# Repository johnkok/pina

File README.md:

# PINA Project - Raspberry Pico-w energy meter

The aim of this project it to create a ultra precise energy meter based on INA228 TI's energy meter device. INA228 is a 20-bit energy meter device, with I2C host interface capable of measuring voltage/current/energy at sampling rates up to 20KHz. Device is connected with a Raspberry Pico W host acquiring the data from the I2C interface and communicating with the host through the WiFi interface using a TCP protocol. In addition, the Pico w module will be able to store IO level on DUT (Device Under Test) and transmit the data to the host application.  
  
On the host side, a basic driver implemented for libsigrok for communicating with the Pico W firmware and propagating the data to sigrok suite. Patched version of sigrok library located at the following location: https://github.com/johnkok/libsigrok

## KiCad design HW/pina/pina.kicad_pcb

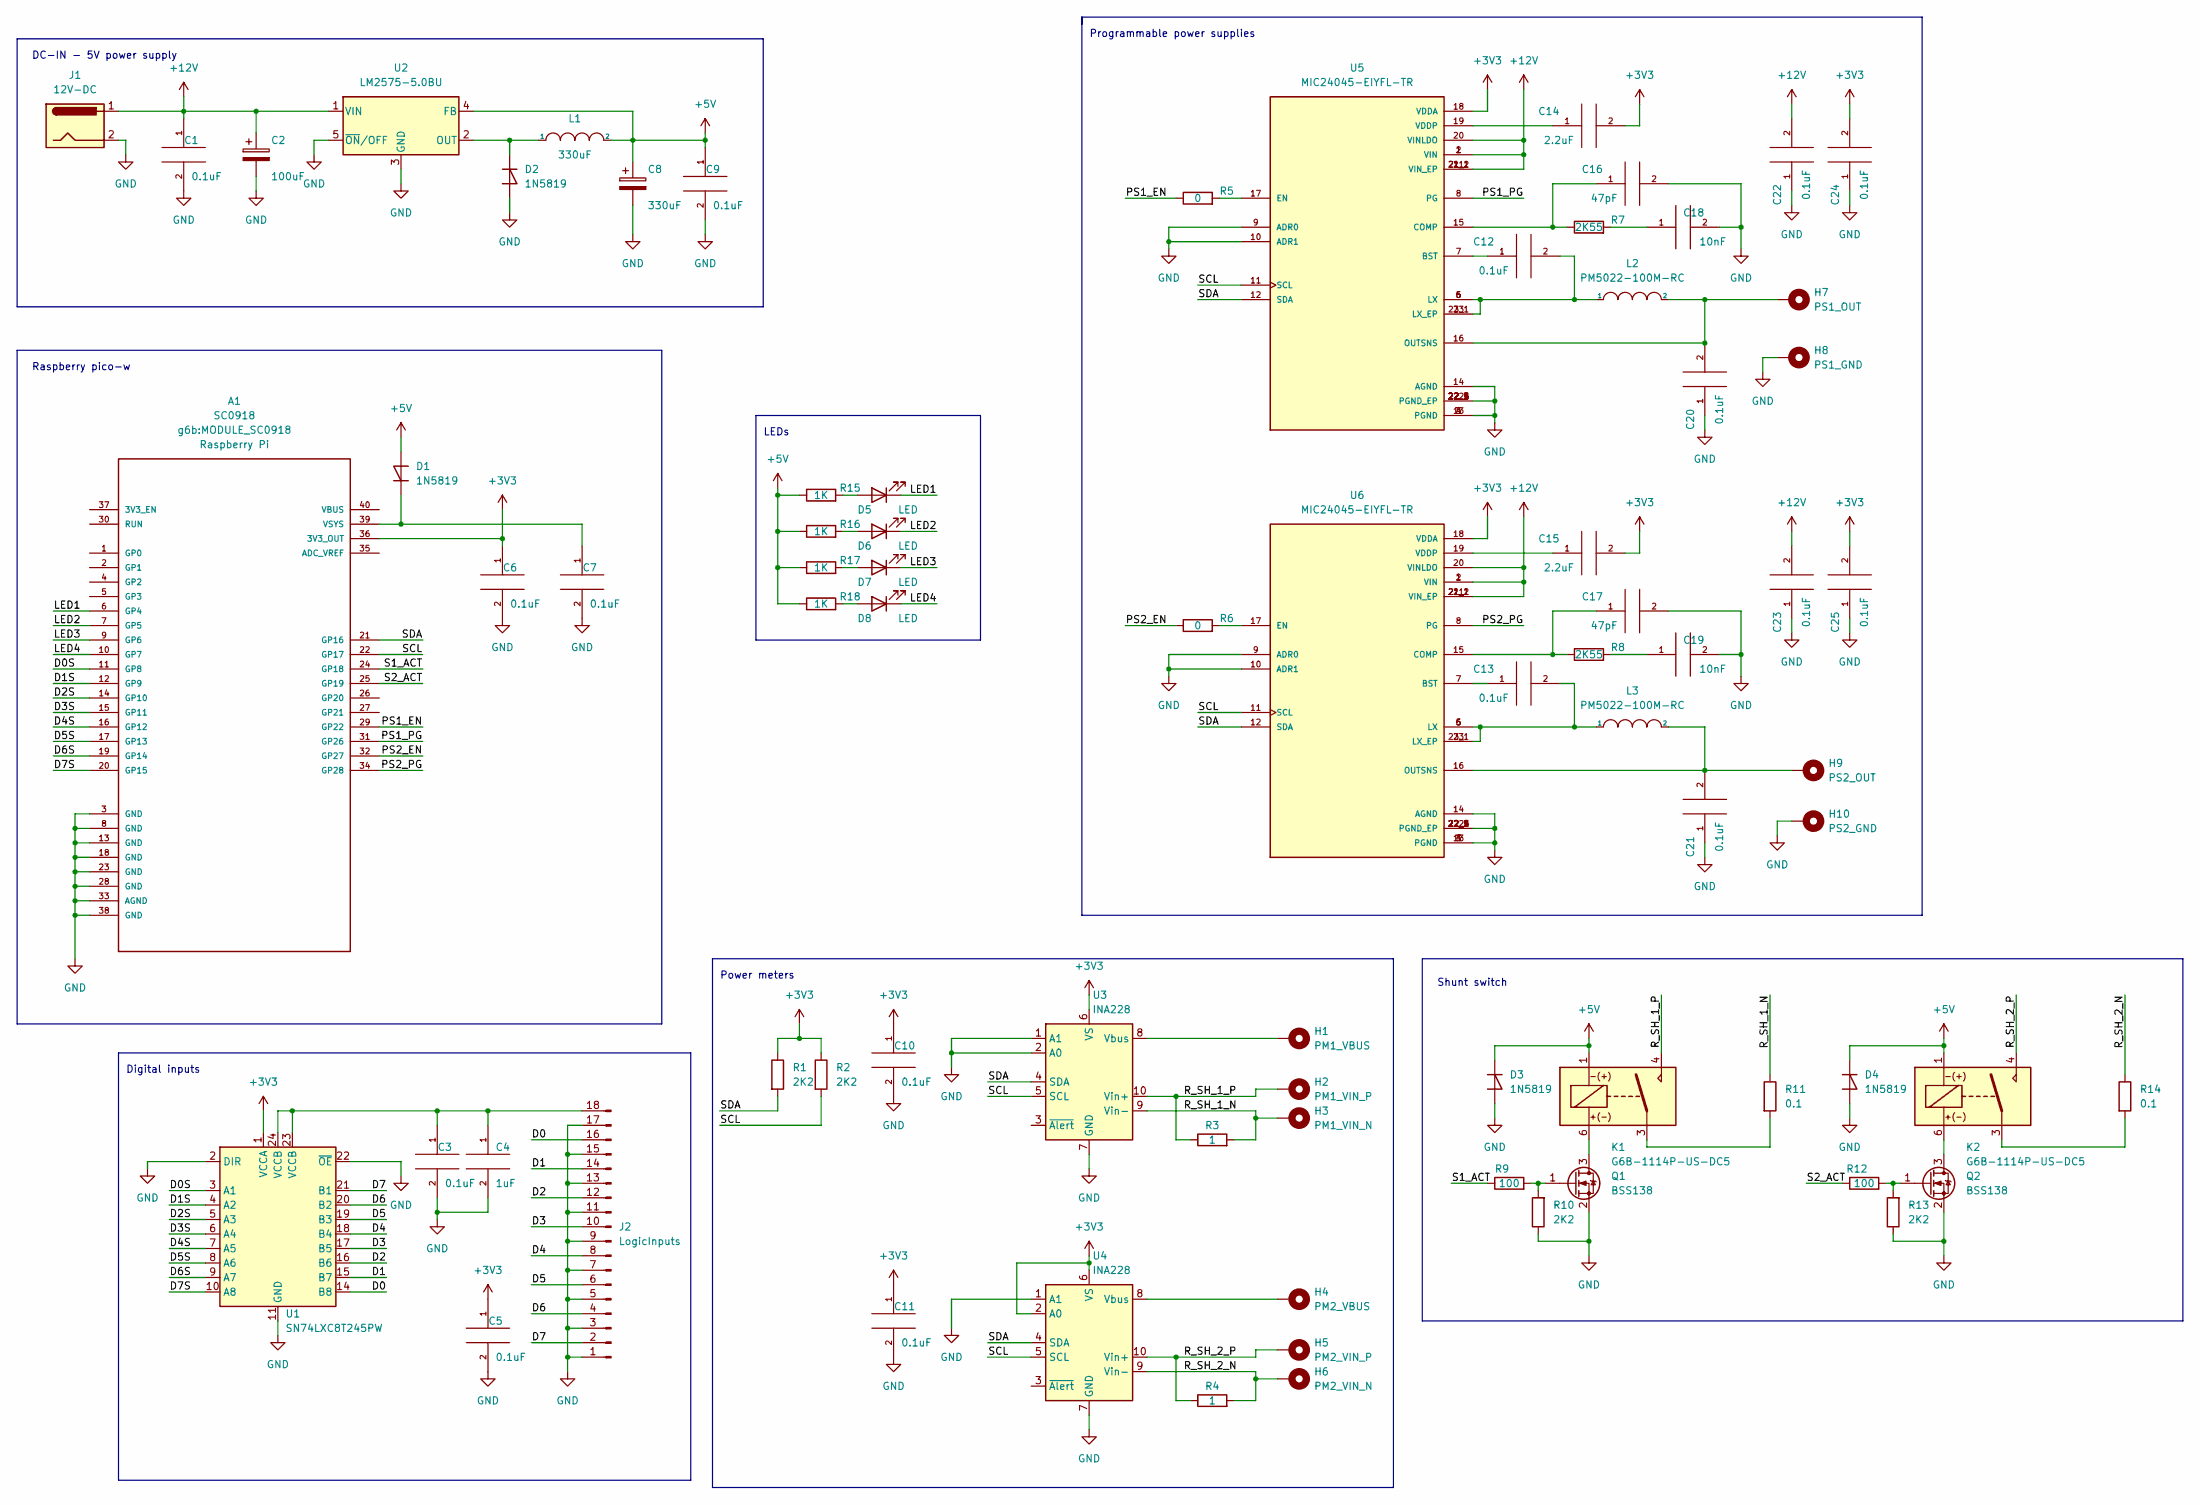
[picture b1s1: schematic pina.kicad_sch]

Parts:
A1: SC0918; MODULE_SC0918; PARTREV 1.6
C1, C3, C5, C6, C7, C9, C10, C11, C12, C13, C20, C21, C22, C23, C24, C25: 0.1uF; C_0603_1608Metric_Pad1.08x0.95mm_HandSolder
C2: 100uF; CP_Elec_8x11.9
C4: 1uF; C_0603_1608Metric_Pad1.08x0.95mm_HandSolder
C8: 330uF; CP_Elec_8x11.9
C14, C15: 2.2uF; C_0805_2012Metric_Pad1.18x1.45mm_HandSolder
C16, C17: 47pF; C_0603_1608Metric_Pad1.08x0.95mm_HandSolder
C18, C19: 10nF; C_0603_1608Metric_Pad1.08x0.95mm_HandSolder
D1, D2, D3, D4: 1N5819; D_SOD-123F
D5, D6, D7, D8: LED; LED_0603_1608Metric_Pad1.05x0.95mm_HandSolder
H1: PM1_VBUS; Banana_Jack_1Pin
H2: PM1_VIN_P; Banana_Jack_1Pin
H3: PM1_VIN_N; Banana_Jack_1Pin
H4: PM2_VBUS; Banana_Jack_1Pin
H5: PM2_VIN_P; Banana_Jack_1Pin
H6: PM2_VIN_N; Banana_Jack_1Pin
H7: PS1_OUT; Banana_Jack_1Pin
H8: PS1_GND; Banana_Jack_1Pin
H9: PS2_OUT; Banana_Jack_1Pin
H10: PS2_GND; Banana_Jack_1Pin
J1: 12V-DC; BarrelJack_GCT_DCJ200-10-A_Horizontal
J2: LogicInputs; PinHeader_2x09_P2.54mm_Vertical
K1, K2: G6B-1114P-US-DC5; RELAY_G6B_1114
L1: 330uF; L_12x12mm_H6mm
L2, L3: PM5022-100M-RC; L_Bourns_SDR1806
Q1, Q2: BSS138; SOT-23
R1, R2, R10, R13: 2K2; R_0603_1608Metric_Pad0.98x0.95mm_HandSolder
R3, R4: 1; R_1206_3216Metric_Pad1.30x1.75mm_HandSolder
R5, R6: 0; R_0603_1608Metric_Pad0.98x0.95mm_HandSolder
R7, R8: 2K55; R_0603_1608Metric_Pad0.98x0.95mm_HandSolder
R9, R12: 100; R_0603_1608Metric_Pad0.98x0.95mm_HandSolder
R11, R14: 0.1; R_1206_3216Metric_Pad1.30x1.75mm_HandSolder
R15, R16, R17, R18: 1K; R_0603_1608Metric_Pad0.98x0.95mm_HandSolder
U1: SN74LXC8T245PW; TSSOP-24_4.4x7.8mm_P0.65mm
U2: LM2575-5.0BU; TO-263-5_TabPin3
U3, U4: INA228; VSSOP-10_3x3mm_P0.5mm
U5, U6: MIC24045-EIYFL-TR; CONV_MIC24045-EIYFL-TR; PARTREV B

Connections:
+3V3: A1.36 (3V3_OUT), C5.1, C6.1, C10.1, C11.1, C14.2, C15.2, C24.2, C25.2, R1.1, R2.1, U1.1 (VCCA), U3.6 (VS), U4.2 (A0), U4.6 (VS), U5.18 (VDDA), U6.18 (VDDA)
+5V: C8.1, C9.1, D1.2 (A), D3.1 (K), D4.1 (K), K1.1, K2.1, L1.2, R15.1, R16.1, R17.1, R18.1, U2.4 (FB)
+12V: C1.1, C2.1, C22.2, C23.2, J1.1, U2.1 (VIN), U5.1 (VIN), U5.2 (VIN), U5.20 (VINLDO), U5.21 (VIN_EP), U5.21_1 (VIN_EP), U5.21_2 (VIN_EP), U6.1 (VIN), U6.2 (VIN), U6.20 (VINLDO), U6.21 (VIN_EP), U6.21_1 (VIN_EP), U6.21_2 (VIN_EP)
/D0: J2.16, U1.14 (B8)
/D0S: A1.11 (GP8), U1.3 (A1)
/D1: J2.14, U1.15 (B7)
/D1S: A1.12 (GP9), U1.4 (A2)
/D2: J2.12, U1.16 (B6)
/D2S: A1.14 (GP10), U1.5 (A3)
/D3: J2.10, U1.17 (B5)
/D3S: A1.15 (GP11), U1.6 (A4)
/D4: J2.8, U1.18 (B4)
/D4S: A1.16 (GP12), U1.7 (A5)
/D5: J2.6, U1.19 (B3)
/D5S: A1.17 (GP13), U1.8 (A6)
/D6: J2.4, U1.20 (B2)
/D6S: A1.19 (GP14), U1.9 (A7)
/D7: J2.2, U1.21 (B1)
/D7S: A1.20 (GP15), U1.10 (A8)
/LED1: A1.6 (GP4), D5.1 (K)
/LED2: A1.7 (GP5), D6.1 (K)
/LED3: A1.9 (GP6), D7.1 (K)
/LED4: A1.10 (GP7), D8.1 (K)
/PS1_EN: A1.29 (GP22), R5.1
/PS1_PG: A1.31 (GP26), U5.8 (PG)
/PS2_EN: A1.32 (GP27), R6.1
/PS2_PG: A1.34 (GP28), U6.8 (PG)
/R_SH_1_N: H3.1, R3.2, R11.1, U3.9 (Vin-)
/R_SH_1_P: H2.1, K1.4, R3.1, U3.10 (Vin+)
/R_SH_2_N: H6.1, R4.2, R14.1, U4.9 (Vin-)
/R_SH_2_P: H5.1, K2.4, R4.1, U4.10 (Vin+)
/S1_ACT: A1.24 (GP18), R9.1
/S2_ACT: A1.25 (GP19), R12.1
/SCL: A1.22 (GP17), R2.2, U3.5 (SCL), U4.5 (SCL), U5.11 (SCL), U6.11 (SCL)
/SDA: A1.21 (GP16), R1.2, U3.4 (SDA), U4.4 (SDA), U5.12 (SDA), U6.12 (SDA)
GND: A1.3 (GND), A1.8 (GND), A1.13 (GND), A1.18 (GND), A1.23 (GND), A1.28 (GND), A1.33 (AGND), A1.38 (GND), C1.2, C2.2, C3.2, C4.2, C5.2, C6.2, C7.2, C8.2, C9.2, C10.2, C11.2, C16.2, C17.2, C18.2, C19.2, C20.1, C21.1, C22.1, C23.1, C24.1, C25.1, D2.2 (A), D3.2 (A), D4.2 (A), H8.1, H10.1, J1.2, J2.1, J2.3, J2.5, J2.7, J2.9, J2.11, J2.13, J2.15, J2.17, Q1.2 (S), Q2.2 (S), R10.1, R13.1, U1.2 (DIR), U1.11 (GND), U1.12 (GND), U1.13 (GND), U1.22 (~OE), U2.3 (GND), U2.5 (~ON/OFF), U3.1 (A1), U3.2 (A0), U3.7 (GND), U4.1 (A1), U4.7 (GND), U5.3 (PGND), U5.4 (PGND), U5.9 (ADR0), U5.10 (ADR1), U5.13 (PGND), U5.14 (AGND), U5.22 (PGND_EP), U5.22_1 (PGND_EP), U5.22_2 (PGND_EP), U5.22_3 (PGND_EP), U5.22_4 (PGND_EP), U5.22_5 (PGND_EP), U6.3 (PGND), U6.4 (PGND), U6.9 (ADR0), U6.10 (ADR1), U6.13 (PGND), U6.14 (AGND), U6.22 (PGND_EP), U6.22_1 (PGND_EP), U6.22_2 (PGND_EP), U6.22_3 (PGND_EP), U6.22_4 (PGND_EP), U6.22_5 (PGND_EP)
unnamed: A1.39 (VSYS), C7.1, D1.1 (K)
unnamed: C3.1, C4.1, J2.18, U1.23 (VCCB), U1.24 (VCCB)
unnamed: C12.1, U5.7 (BST)
unnamed: C12.2, L2.1, U5.5 (LX), U5.6 (LX), U5.23 (LX_EP), U5.23_1 (LX_EP)
unnamed: C13.1, U6.7 (BST)
unnamed: C13.2, L3.1, U6.5 (LX), U6.6 (LX), U6.23 (LX_EP), U6.23_1 (LX_EP)
unnamed: C14.1, U5.19 (VDDP)
unnamed: C15.1, U6.19 (VDDP)
unnamed: C16.1, R7.1, U5.15 (COMP)
unnamed: C17.1, R8.1, U6.15 (COMP)
unnamed: C18.1, R7.2
unnamed: C19.1, R8.2
unnamed: C20.2, H7.1, L2.2, U5.16 (OUTSNS)
unnamed: C21.2, H9.1, L3.2, U6.16 (OUTSNS)
unnamed: D2.1 (K), L1.1, U2.2 (OUT)
unnamed: D5.2 (A), R15.2
unnamed: D6.2 (A), R16.2
unnamed: D7.2 (A), R17.2
unnamed: D8.2 (A), R18.2
unnamed: H1.1, U3.8 (Vbus)
unnamed: H4.1, U4.8 (Vbus)
unnamed: K1.3, R11.2
unnamed: K1.6, Q1.3 (D)
unnamed: K2.3, R14.2
unnamed: K2.6, Q2.3 (D)
unnamed: Q1.1 (G), R9.2, R10.2
unnamed: Q2.1 (G), R12.2, R13.2
unnamed: R5.2, U5.17 (EN)
unnamed: R6.2, U6.17 (EN)

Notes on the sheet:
DC-IN - 5V power supply
LEDs
Programmable power supplies
Raspberry pico-w
Power meters
Shunt switch
Digital inputs

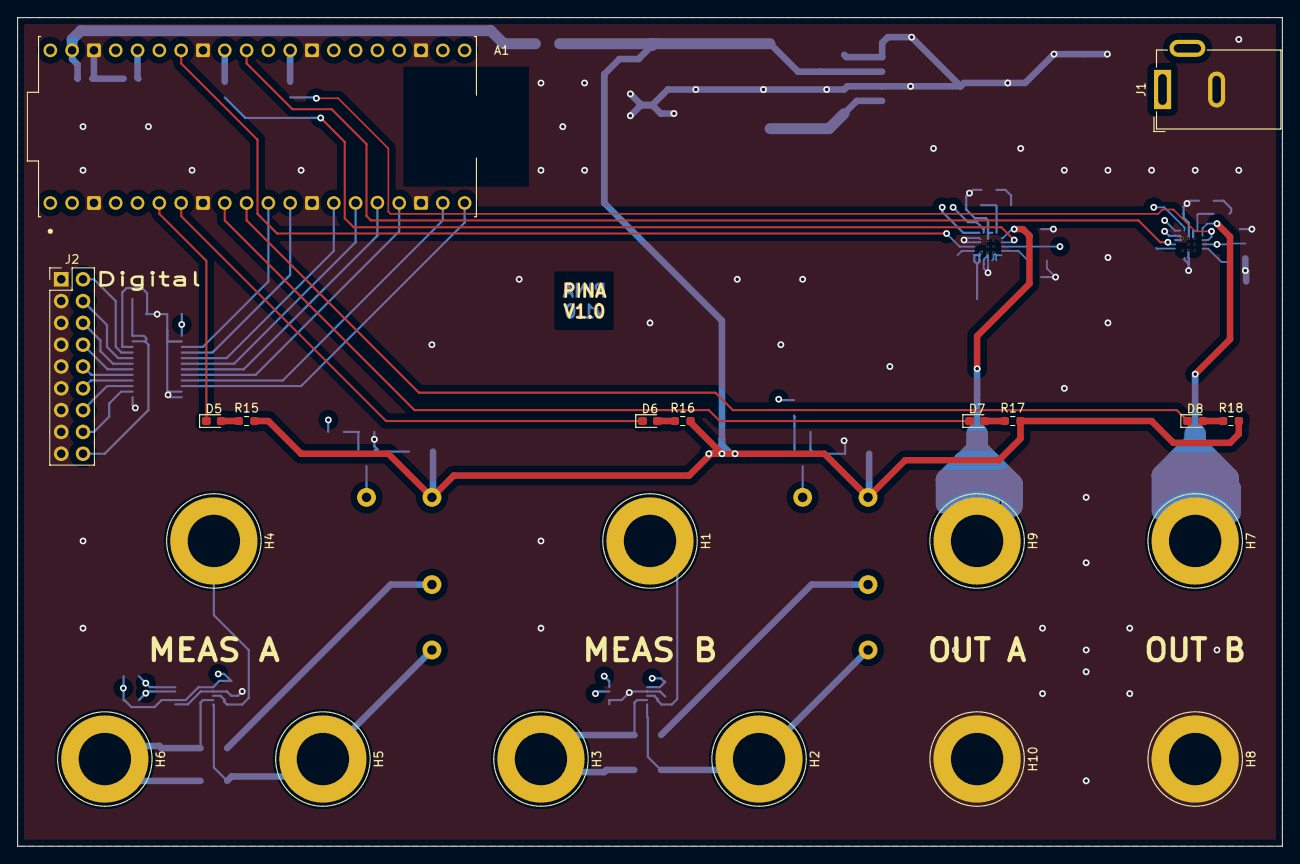
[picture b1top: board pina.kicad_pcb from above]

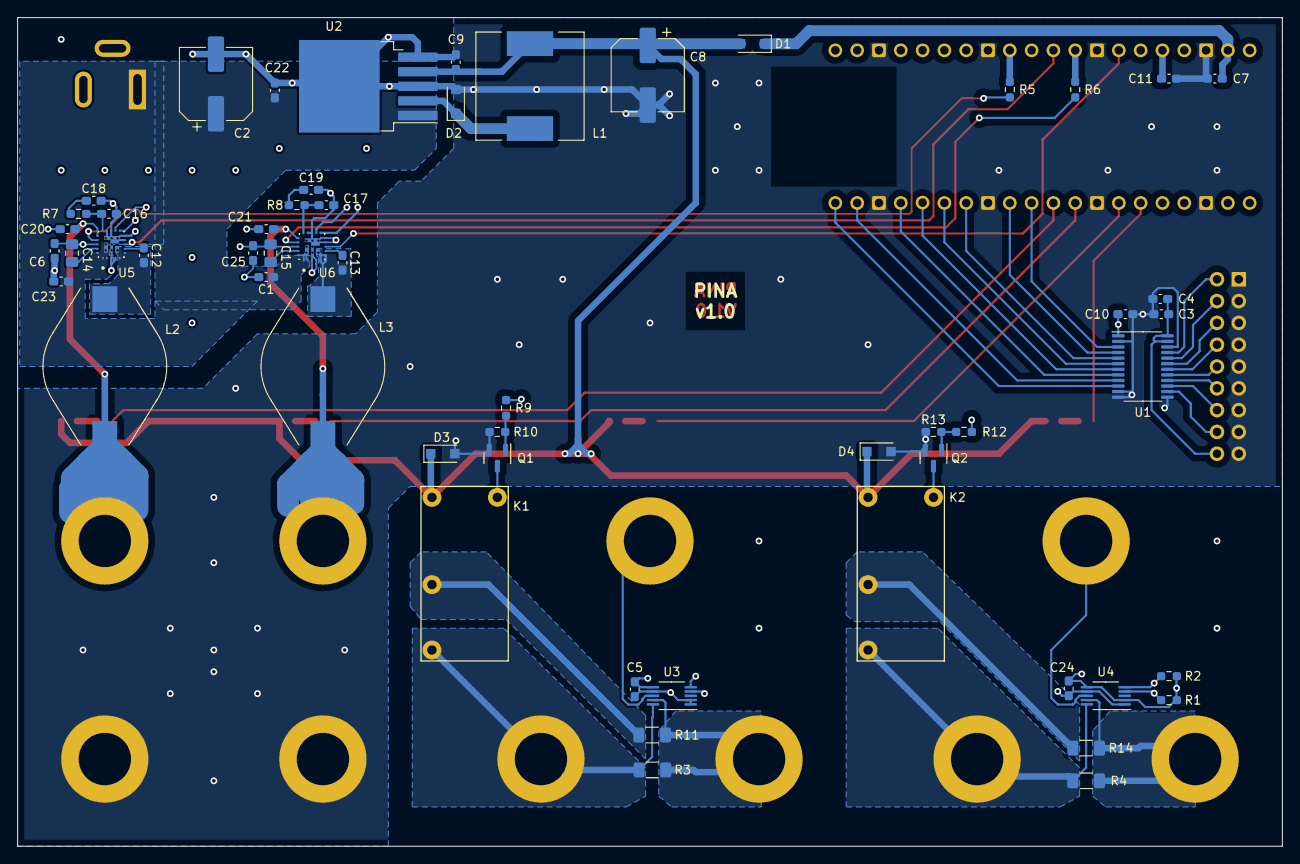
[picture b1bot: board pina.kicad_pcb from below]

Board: 4 copper layers, 147.3 x 96.5 mm, 77 parts (56 on the bottom side), 65 nets.

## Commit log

2022-12-21 add test server
2022-12-21 update doc
2022-12-28 pico initial FW added
2022-12-28 fix pico FW
2023-01-22 Initial schematic added
2023-01-29 Initial pcb added
2023-01-30 PCB finalized
2023-02-25 Update PCB
